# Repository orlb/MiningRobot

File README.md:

# UAF Robot Control Architecture, 2023 Version
## Codebase
The autonomy/ directory contains our robot control stack, written in C++ for Linux and running happily on x86 and ARM based robots including the Raspberry Pi or NVIDIA Jetson.  See the README in that directory for build directions.

## LUNATIC
The "Logically UNcoupled Architecture Technology for Intra-robot Communication" or LUNATIC (pronounced lun-AT-ic, like automatic) is our robot control system, built as a loosely coupled set of microservices.

Using microservices means you can compile, run, and test a single service independently, unlike our previous single monolithic executable the [backend](autonomy/backend/main.cpp).  

Due to the nature of a robotics control stack, being able to efficiently exchange quickly changing data between modules is crucial. We do this using the new MMAP-based shared file data exchange system, the details of which can be found in the [data_exchange.h](autonomy/include/aurora/data_exchange.h) header. 

The data being exchanged is listed in the [lunatic.h](autonomy/include/aurora/lunatic.h) header for the microservices, and [nanoslot_exchange.h](autonomy/nanoslot/include/nanoslot/nanoslot_exchange.h) for the Arduino data.

## Control Software Stack
A basic manual control setup has autonomy/frontend running on the "pilot" machine, and sending commands to the autonomy/backend running onboard the robot.  These commands are sent via UDP broadcast, so they should work anywhere on the same subnet.  The backend talks to the Arduinos directly via USB--each Arduino has a "nanoslot ID" that lets nanoboot connect the appropriate slot program to communicate with it.  To control the robot, all you need is a backend and the slot programs: put the backend into "backend driver" state, and use WASD to drive the robot.

For autonomous robot operations, we rely on a huge variety of microservices, such as the localizer (where is the robot?), path planner (how do we get to the target?), andretti (how do we drive along the path?), vision (what obstacles can we see?), and several other debug tools.

This architecture has been incrementally built up since 2013 by a variety of UAF students for the NASA Robotic Mining Contest.  Unless otherwise noted, everything here is public domain. 

For details on how build and run this software, see autonomy/README.
Send a pull request or email lawlor@alaska.edu if you have comments or suggestions!

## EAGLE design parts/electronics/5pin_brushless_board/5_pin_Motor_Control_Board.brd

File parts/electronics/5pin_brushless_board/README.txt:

5-pin Brushless motor control board
Designed as a direct plug-compatible replacement for the UN178 brushed motor controller, to let us mix and match brushed/brushless motors. 
Designed in summer 2022 by Daniel Kling

Designed in Autodesk EAGLE (free version limited to 12.4 square inches, this board is under 5 square inches). 

Board input: same male DIP (2.54mm pin spacing) 2x5 pin grid as the UN178. 

Board mounting: same M3 screw holes as UN178, at least the left two.  Probably doesn't need to be as big as the UN178.

Board style: ideally large trace (0.8mm trace width minimum), single layer back side copper only to allow local fabrication on a CNC mill if needed. Can use front side copper traces as occasional jumpers, which just work on a commercially fabricated board, and we can make ourselves using jumpers. 

Board outputs: probably a row of 3-pin male DIP 1x3 pin headers, which would let us plug in R/C ESC or servo headers directly.  Should be able to do like 5 outputs for different motors or encoders/sensors/etc.

5-pin output pinout:
	GND pin shared across all outputs
	5v pin shared across all outputs, fed from a non-PWM Arduino I/O pin?  (I don't think I have a 5V on the header right now)
	Signal pin, from individual Arduino I/O pins
	(so far, this is a 3-pin R/C servo connector)
	12/24V + motor supply pin (for motors only needing a few amps)
	gnd motor supply pin

Dupont pins are limited to 1-3 amps maximum (depending on the exact pin). 
For big motors, like drive or mine motors, they'll only take the 3-pin R/C plug and run dedicated motor supply wires.

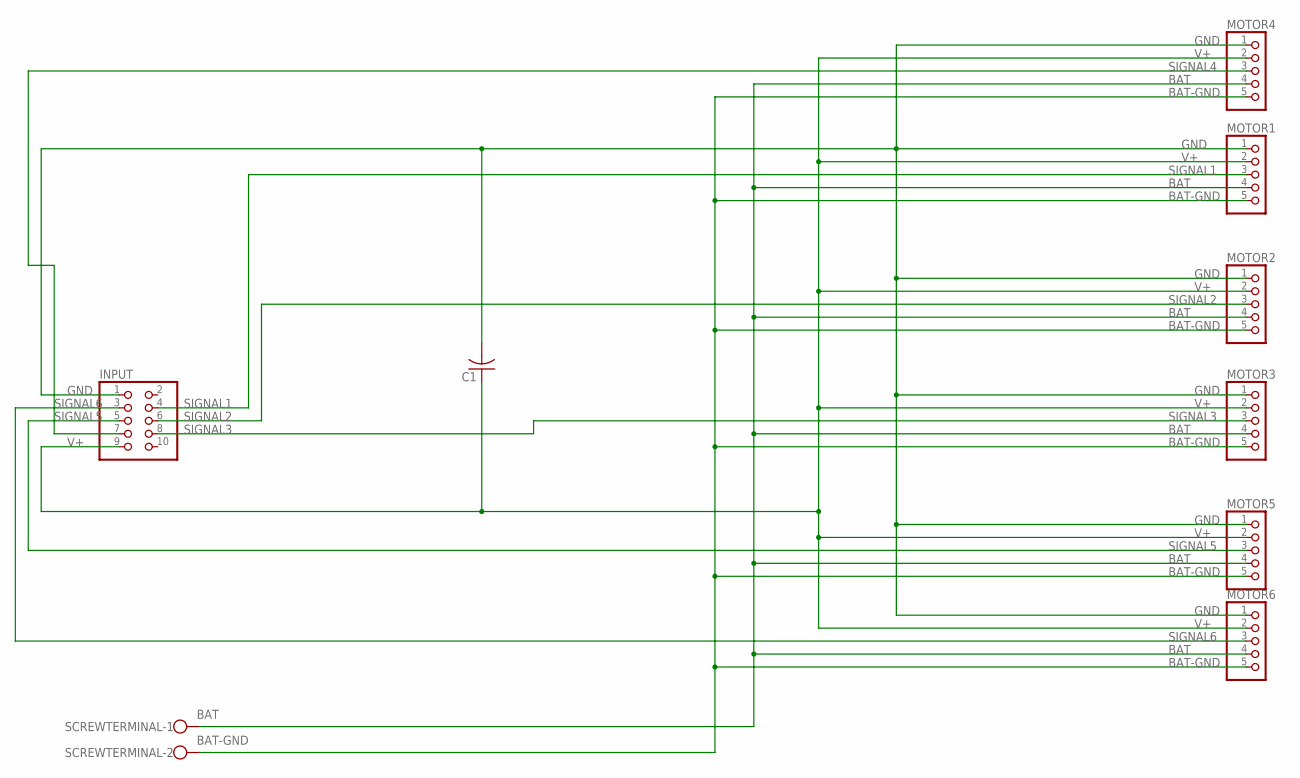
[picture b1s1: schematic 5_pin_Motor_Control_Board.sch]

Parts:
C1: C-US025-025X050; C025-025X050
INPUT: PINHD-2X5; 2X05
MOTOR1, MOTOR2, MOTOR3, MOTOR4, MOTOR5, MOTOR6: PINHD-1X5; 1X05
SCREWTERMINAL: W237-102

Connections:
BAT: MOTOR1.4, MOTOR2.4, MOTOR3.4, MOTOR4.4, MOTOR5.4, MOTOR6.4, SCREWTERMINAL.1
BAT-GND: MOTOR1.5, MOTOR2.5, MOTOR3.5, MOTOR4.5, MOTOR5.5, MOTOR6.5, SCREWTERMINAL.2
GND: C1.2, INPUT.1, MOTOR1.1, MOTOR2.1, MOTOR3.1, MOTOR4.1, MOTOR5.1, MOTOR6.1
SIGNAL1: INPUT.4, MOTOR1.3
SIGNAL2: INPUT.6, MOTOR2.3
SIGNAL3: INPUT.8, MOTOR3.3
SIGNAL4: INPUT.7, MOTOR4.3
SIGNAL5: INPUT.5, MOTOR5.3
SIGNAL6: INPUT.3, MOTOR6.3
V+: C1.1, INPUT.9, MOTOR1.2, MOTOR2.2, MOTOR3.2, MOTOR4.2, MOTOR5.2, MOTOR6.2

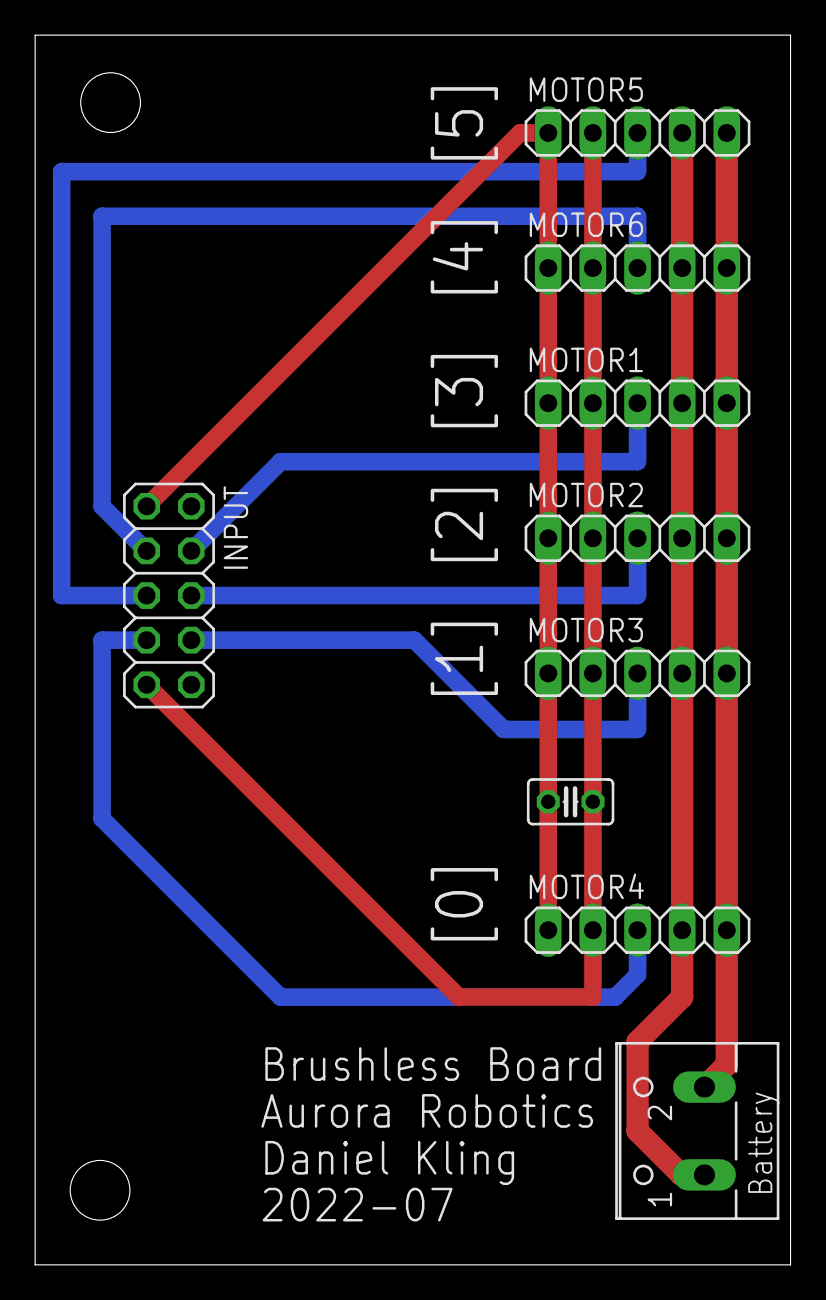
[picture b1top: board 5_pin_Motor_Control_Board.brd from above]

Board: 2 copper layers, 43.0 x 70.0 mm, 9 parts (0 on the bottom side), 10 nets.

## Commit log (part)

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2022-04-16 Boot into Break The Ice robot configuration (for direct backend_driver)
2022-04-16 Add support for monitoring via "conky".
2022-04-16 Update ArUco camera calibration for OpenCV4
2022-04-16 Boot with power level 0.6, for reasonable driving without a keyboard.
2022-08-13 Boot robot into full power driving (for backend, where you don't have a keyboard to adjust the power.)
2023-01-24 New approach to PC-arduino communication, allowing hotplug of many devices.
2023-01-26 Added example slot EE, to demonstrate multiple Arudinos and hotplug.
2023-01-28 Color swap: blue for safe (stopped), yellow for manual driving, red for autonomous.
2023-01-30 Move to obsolete old kend (now nanoslot), firmware (ancient, for mega), nano_firmware (now nanoslot firmwares).
2023-01-30 Add ArduinoJson library, for use by server code.
2023-01-30 Replace macros in nanoslot interface with classes, interface is much cleaner now.
2023-02-01 Print precision-reduced acclerometer & gyro data (remove noise bits)
2023-02-02 Add firmware_mpu6050 interface to inertial measurement unit (IMU).
2023-02-09 Add "state" member to nanoslot data structures, for things like filtered / cleaned IMU data.
2023-02-11 Minor updates: enable I2C Wire timeout, handle IMU disconnects more gracefully.
2023-02-27 Update robot power struct and autonomy states to match break the ice robot.
2023-03-02 Update control channels to match physical hardware, and rational control directions.
2023-03-03 Add softlink to nanoslot header files (thank you Bryan for the report!).
2023-03-04 Update autonomy stack diagram for new nanoslot Arduino comm architecture.
2023-03-04 Update README to describe current nanoslot architecture.
2023-03-05 Move RealSense T265 support out of mainline. This may come back if odometry isn't reliable.
2023-03-06 Fix encoders in --sim backend mode (didn't get updated from power scaling from percent to +-1.0).
2023-03-06 add lunatic_capture_data.cpp and update makefile
2023-03-06 Print backend state (placeholder, more state coming!)
2023-03-06 add json.hpp in hlohmann dir in /include, and add to lunatic_capture_data.cpp
2023-03-07 Update comments on each file to clarify what it does, and why.
2023-03-08 add commented code from old json project to lunatic_capture_data.cpp
2023-03-08 debug makefile and set abbrevation for filesystem namespace
2023-03-08 debug first 48 lines of code in lunatic_capture_data.cpp, add debug output file, update .gitignore in lunabug dir
2023-03-08 update time to take into account milliseconds, to allow for milliseconds in file name separation
2023-03-09 Check in slot F1 (like A1, but with 4 IMUs).
2023-03-10 Fix the bug Brandon encountered today, where the slot program gave up before the Arduino bootloader finished booting.
2023-03-10 Remove accidental commit of slot binary program.
2023-03-10 Add directions to copy over librealsense udev rules. Works on the Pi!
2023-03-10 Add directions for installing nanoslot udev scripts (important for robot, not needed for development.)
2023-03-11 Add drive motor nanoslot D0, and update Makefile with new slots.
2023-03-12 Add IMU filtering, based on a heavily modified Madgwick library: https://github.com/xioTechnologies/Fusion
2023-03-12 Move nanoslot headers from autonomy/nanoslot/include to top-level autonomy/include (so IMU code can use vec3).
2023-03-13 Initial kinematic support, and 3D model of robot for debugging.
2023-03-13 Minimal frontend updates for new display architecture. (Still need to add joint angles to robot_base to display them.)
2023-03-13 Rework robot_base so it carries joint angles too, and use robot_base for backend_state and network telemetry directly instead of copying every field over.
2023-03-13 add createNewFile() to lunatic_capture_data.cpp
2023-03-13 develop data storage functions in lunatic_capture_data.cpp
2023-03-13 develop functions in lunatic_capture_data.cpp
2023-03-14 establish basic datastreaming in jupyter notebook
2023-03-14 Updated IMU handling code, it works on the physical hardware now!
2023-03-15 Read from load cells via HX711 chip: firmware, slot changes. Also show coordinate axis via new kinematics functions.
2023-03-16 New "vision_mining.cpp" that extracts depth camera data for planning mining. Also IMU calibration improvements (scale factor).
2023-03-17 add all necessary vars to data capture
2023-03-18 add test database connection code
2023-03-18 prep json variable with robot data
2023-03-18 update root .gitignore to ignore temporary swp files
2023-03-18 debug lunacapture.cpp to successfully compile
2023-03-18 Remove lunatic_capture_data from lunabug makefile, so everything builds.
2023-03-19 Update simulator to respect as-built hardware joint angle limits.
2023-03-19 prep database insert command and capture time as uint from epoch instead
2023-03-19 debug capture_epoch()
2023-03-20 change transaction_base to work, debug sql typo
2023-03-23 AUTONOMOUS MINING! Very crude proportional-only control, but it follows the depth seen in vision. Works in sim, needs real robot test.
2023-03-24 Minor refactoring of scoop & arm move code, to match real robot parameters.
2023-04-06 restructure folder dir to accommodate for data viewer
2023-04-06 initiate simple QPlot app
2023-04-06 Add load cell control, with weigh state collecting left and right total in scoop.
2023-04-07 add BUILD.md, develop q plot
2023-04-07 Remove "JSONB", because it inflates the on-disk data size by 5x.
2023-04-08 Update drive nanoslot D0 to work with updated nanoslot_exchange.
2023-04-12 Support software-controlled excavation by routing power.tool to new slot C0.
2023-05-04 develop jupyter notebook for database visualization
2023-05-06 Calibrated logitech C920 webcam for 1280x720 resolution (now the default).
2023-05-08 import and access data from database using sqlalchemy
2023-05-09 establish functions to call last item of database
2023-05-09 add two decimal place rounding to angles, continue developing live data display
2023-05-10 develop live feed graph
2023-05-10 separate out .cpp and .hpp files for clarity
2023-05-10 test .dbpass variable add
2023-05-12 add capability for two live graphs for comparison
2023-05-12 move title draw elements to while loop
2023-05-14 remove test file, add title comment to lunacapture.cpp
2023-05-14 remove errors from bluesanta-dev branch
2023-05-14 remove error imported from bluesanta-dev branch
2023-05-14 Updated documentation from our experience building on the real robot.
2023-05-15 add html snapshot of luna_canvas
2023-05-15 redo graphs for visual display purposes
2023-05-18 remove TO DO messages and implement new instance_num column in db
2023-05-20 develop implementation of instance_num var
2023-05-27 Fix bug where first run with an empty database would hang.
2023-05-27 Include load cell data, and use function for rounding to two decimal places.
2023-05-28 added warnings and prompts to console
2023-05-28 Rearrange script variables so they're more self-documenting, and only need one sudo call.
2023-05-29 Move confusing backend.sh (uses old systemd method) to service_backend.sh
2023-05-29 Remove spare json file (why did this end up in the repo?).
2023-05-31 add export failed message
2023-06-02 update capture_epoch() to uint64_t to allow for correct time in milliseconds
2023-06-06 move round() function to .hpp/.cpp files
2023-06-06 cleaning up libraries
2023-06-06 clean libraries in main.cpp
2023-06-06 small formatting adjustment
2023-06-08 parse json into data columns in database
2023-06-08 rename lunascratch to lunascratch-qt to allow for other scratch projects
2023-06-14 Fix voltage bias for F0 to agree with calibrated battery monitor.
2023-06-15 Actually read drive encoders, and fix mine encoder spinrate calculation.
2023-06-17 Add script to reboot the USB stack, if devices disconnect themselves again.
2023-06-20 Update charge estimate with actual on-robot measurements.
2023-06-25 UI improvements: move arm in mine mode, more readable background colors.
2023-06-28 Update robot_3D_draw calls for new tool interface.
2023-07-02 Tuned parameters on actual robot.
2023-07-02 remove old qt files and folders
2023-07-02 Added data columns for battery and accumulated data. Also simplified data column addition to lunacapture main only.
2023-07-03 When the backend disconnects, print a message in the frontend saying so. (Could stand more difference, such as a black background.)
2023-07-06 Add 3D localization to robot_base, and STL file capture for depth data.
2023-07-15 Only use 4 decimal places in STL, 0.1mm precision is way better than the depth camera data.
2023-07-18 Display localization in meters, on very large field for demonstration.
2023-07-18 Backend ignores tool roll value, which is bogus (probably an IMU bug, but not obvious what it is!).
2023-07-18 Simplify user interface handling in prep for POP state. Now just two joystick modes: low (drive and scoop) and high (arm and tool).
2023-07-19 Remove duplicate depth image erosion code to a new header.
2023-07-19 Adjust display order so the location of the robot always appears even if the sideview is on top of it.
2023-07-20 Fix time to be seconds, not a million times faster (bug introduced with --nogui).
2023-07-20 Restore old state accum data on startup, so we don't lose the daily totals because we needed to fix something in autonomy.
2023-07-21 Slightly wider field of view, so the robot is visible when parked.
2023-07-24 Go back to logging to the database every half second, this is plenty and the database gets big already.
2023-07-24 Start a backend with no GUI by default in the start script (this works too well to not use!).
2023-07-24 Rework sensors to include frame angles, operation time, joint plans.
2023-07-25 Shrink the displayed window down, allowing vision to work over slow SSH connection.
2023-07-25 Updated hauling back and forth, ready for test on real robot!
2023-07-25 Better print formatting for new telemetry fields.
2023-07-26 Adjust confidence percentages more conservatively when viewing markers.
2023-07-26 Plan mining path as a fixed angle. Also updated kinematic limits to reflect reality.
2023-07-26 Display joint_plan with alpha transparency.
2023-07-26 Fix print bug: robotPrintln re-interpreted % as printf format. (This stuff is a mess.)
2023-07-27 Tuned autonomous mining, it now runs on the real robot surprisingly well!
2023-07-27 Adjust display downscaling, start considering vision-based cut alignment.
2023-07-28 Adjust autonomous mining parameters to give better real-world results.
2023-07-28 'v'+digit allows half-centimeter cuts (c+3 = 3.0 or "cut 3", v+3 = 3.5 or "very 3").
2023-07-29 Not working yet trig-based automated driving. (Checking in so I can dev this in sim, not on the real robot...)
2023-07-29 Add --sim flag that makes confidence a high fixed value.
2023-07-29 More conservative drive distance estimate, from localizer instead of just encoders.
2023-07-30 Tuning new robot configuration (2 of ???).
2023-07-30 Tuning (4 of ???)
2023-07-30 Cut a bit more confidently, moving back more rapidly once spinning.
2023-07-30 Squash warning by defining a constant array length.
2023-07-31 Tuned mining and 'weigh' operations to work more reliably.
2023-08-02 Initialize localizer at the start of the haul run, so we can do more reasonable haul path without camera support.
2023-08-04 Check in uhubctl for transport onto robot.
2023-08-04 Added uhubctl power to USB scripts (needs testing to verify this clears webcam or IMU errors like an unplug/replug).
2023-08-06 Final on-robot fixes for day 15 of the durability demo.
2023-08-08 Minor fix required to make joystick work even in --nogui mode.
2023-09-03 Added "joint_move_hazards" to prevent the robot hitting the scoop with the tool, or electronics box with the arm.
2023-09-05 Fixed formatting of previous addition
2023-09-20 Fix compile bug if you're not building backend (just an #ifdef for now)
2023-10-04 Added collision detection for tool on boom and frame.
2023-10-10 Added collision checking for tool back and bottom on upper corner of scoop.
2023-10-11 Removed redundancy.
2023-10-14 ros2_workspace and ros2_ouster_drivers build
2023-10-15 Successful test reading robot backend state from ROS2 node
